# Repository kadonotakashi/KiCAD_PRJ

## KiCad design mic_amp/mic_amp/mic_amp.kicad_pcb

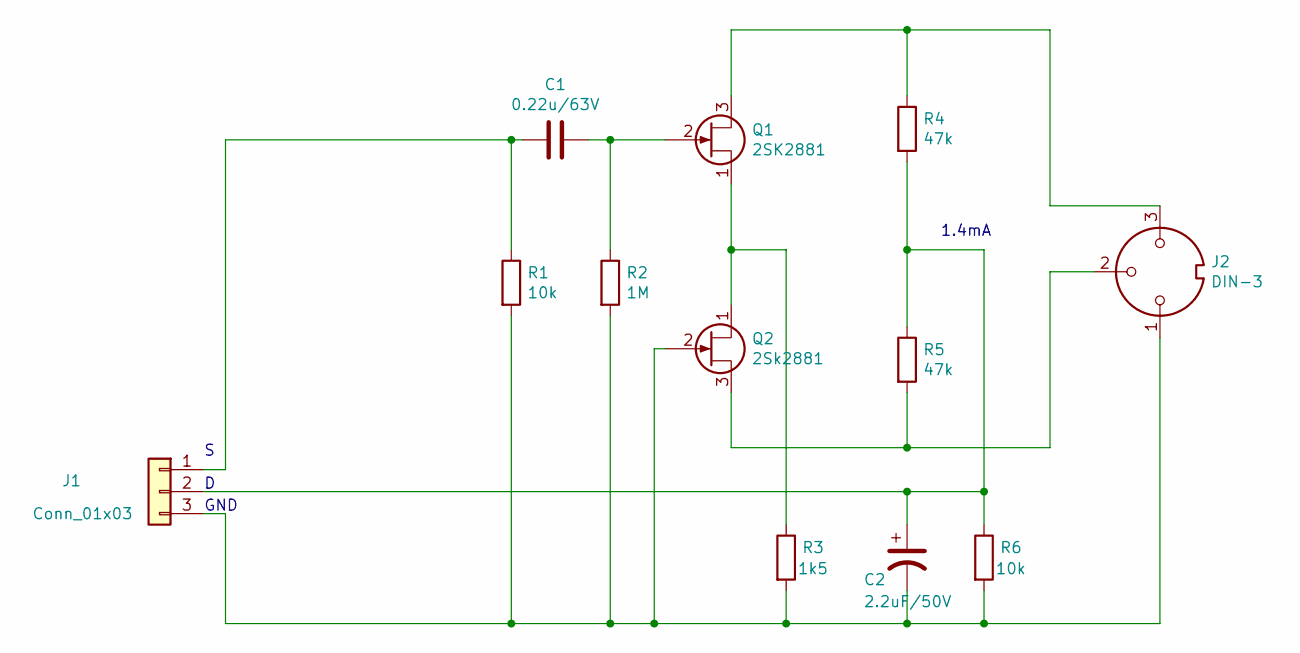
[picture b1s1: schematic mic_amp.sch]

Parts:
C1: 0.22u/63V; C_Disc_D7.5mm_W4.4mm_P5.00mm
C2: 2.2uF/50V; C_Radial_D5.0mm_H7.0mm_P2.00mm
J1: Conn_01x03; PinHeader_1x03_P2.54mm_Vertical
J2: DIN-3; PinHeader_1x03_P2.54mm_Vertical
Q1: 2SK2881; TO-92_Inline_Wide
Q2: 2Sk2881; TO-92_Inline_Wide
R1, R6: 10k; R_Axial_DIN0204_L3.6mm_D1.6mm_P7.62mm_Horizontal
R2: 1M; R_Axial_DIN0204_L3.6mm_D1.6mm_P7.62mm_Horizontal
R3: 1k5; R_Axial_DIN0204_L3.6mm_D1.6mm_P7.62mm_Horizontal
R4, R5: 47k; R_Axial_DIN0204_L3.6mm_D1.6mm_P7.62mm_Horizontal

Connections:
unnamed: C1.1, Q1.2 (G), R2.1
unnamed: C1.2, J1.1, R1.1
unnamed: C2.1, J1.2, R4.2, R5.1, R6.1
unnamed: C2.2, J1.3, J2.1, Q2.2 (G), R1.2, R2.2, R3.2, R6.2
unnamed: J2.2, Q2.3 (D), R5.2
unnamed: J2.3, Q1.3 (D), R4.1
unnamed: Q1.1 (S), Q2.1 (S), R3.1

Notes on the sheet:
1.4mA
GND

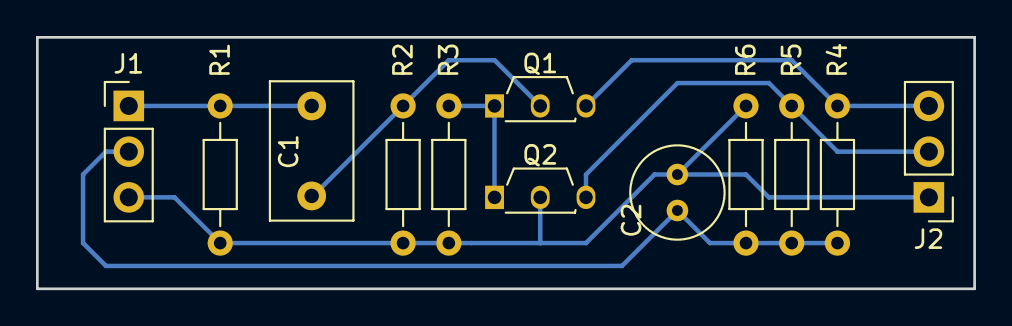
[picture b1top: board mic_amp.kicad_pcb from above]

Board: 2 copper layers, 52.1 x 14.0 mm, 12 parts (0 on the bottom side), 7 nets.

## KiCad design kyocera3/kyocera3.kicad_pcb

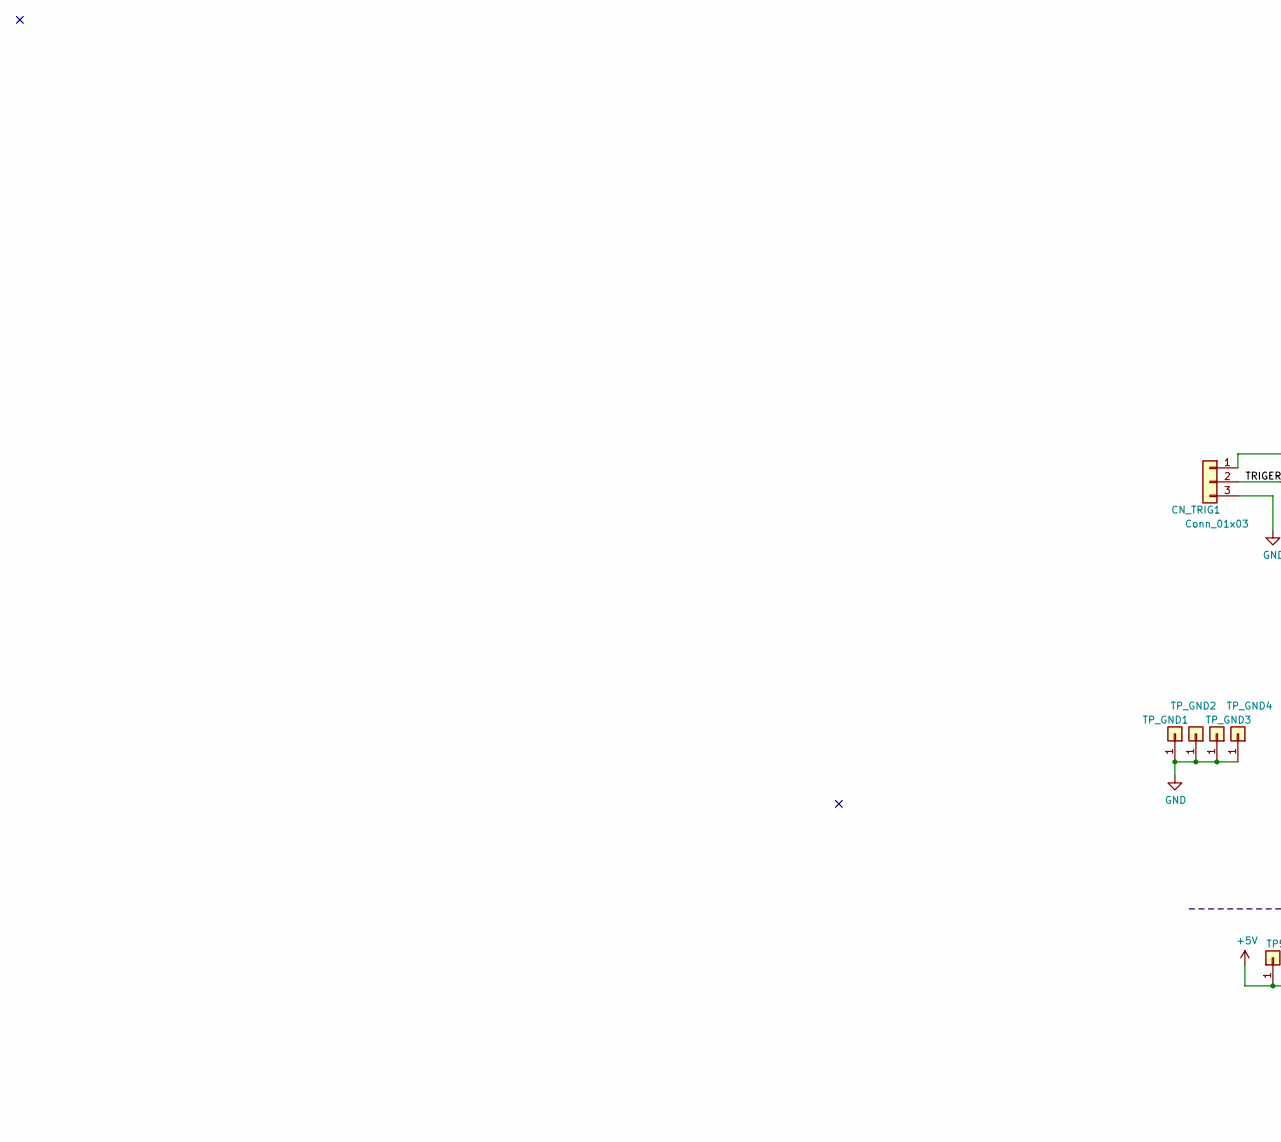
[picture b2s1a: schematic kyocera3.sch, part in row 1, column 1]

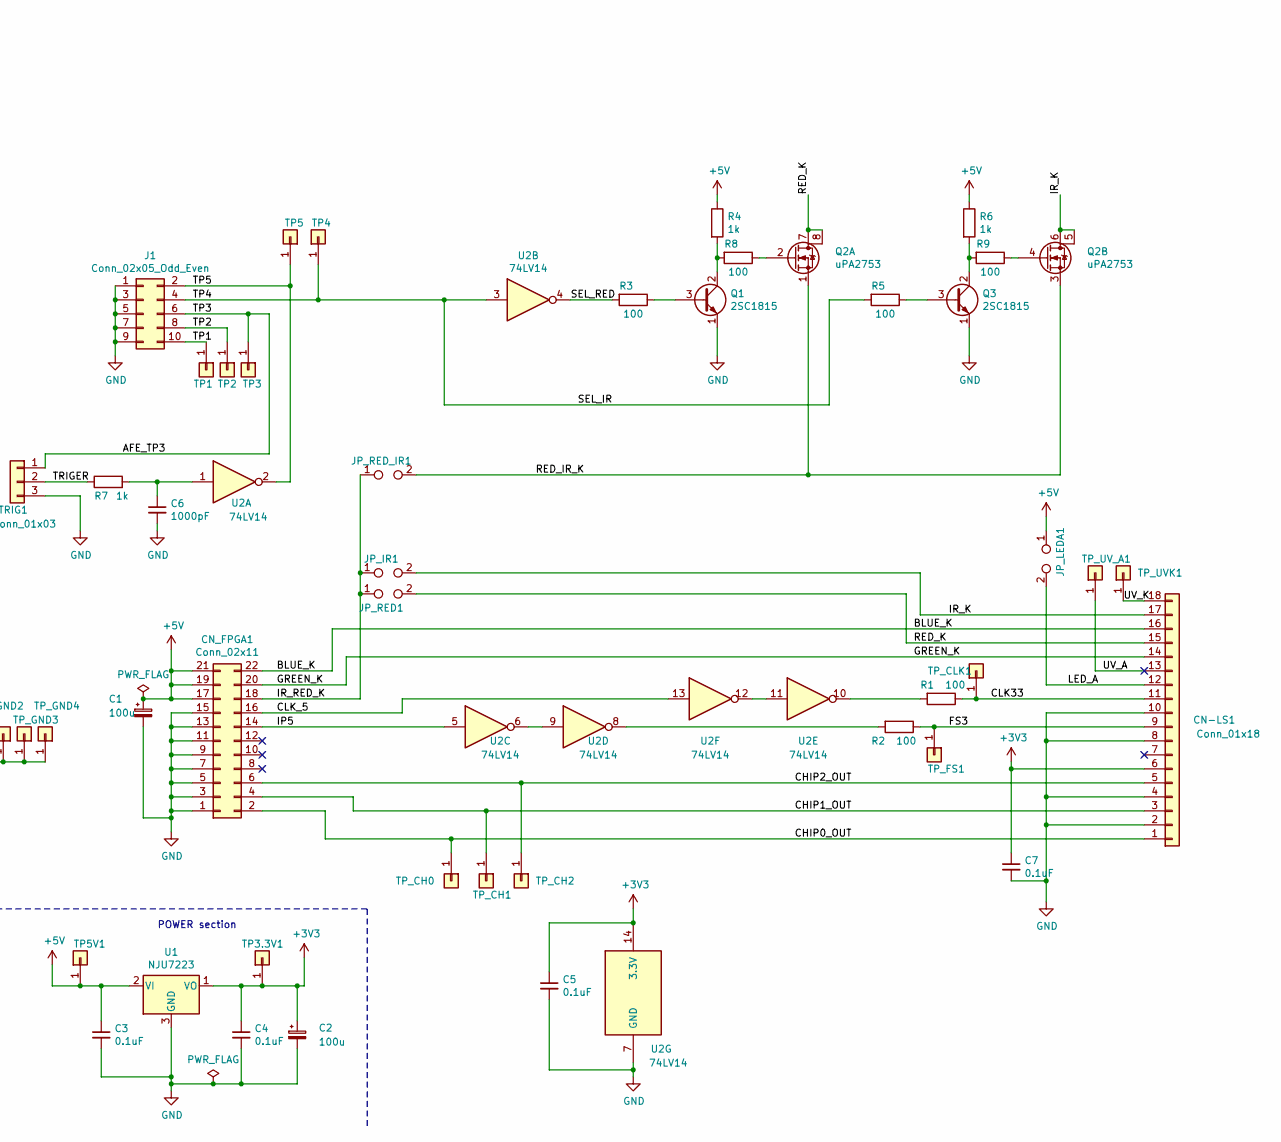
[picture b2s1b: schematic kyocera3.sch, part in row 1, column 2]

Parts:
C1, C2: 100u; CP_Radial_D6.3mm_P2.50mm
C3, C4, C5, C7: 0.1uF; C_0805_2012Metric_Pad1.15x1.40mm_HandSolder
C6: 1000pF; C_0805_2012Metric_Pad1.15x1.40mm_HandSolder
CN-LS1: Conn_01x18; TE_1-84953-8_1x18-1MP_P1.0mm_Horizontal
CN_FPGA1: Conn_02x11; PinHeader_2x11_P2.54mm_Vertical
CN_TRIG1: Conn_01x03; JST_EH_S03B-EH_1x03_P2.50mm_Horizontal
J1: Conn_02x05_Odd_Even; PinHeader_2x05_P2.54mm_Vertical
JP_IR1: IR; PinHeader_1x02_P2.54mm_Vertical
JP_LEDA1: IR; PinHeader_1x02_P2.54mm_Vertical
JP_RED1: RED; PinHeader_1x02_P2.54mm_Vertical
JP_RED_IR1: IR; PinHeader_1x02_P2.54mm_Vertical
Q1, Q3: 2SC1815; TO-92_Inline
Q2: uPA2753; SOIC-8_3.9x4.9mm_P1.27mm
R1, R2, R3, R5, R8, R9: 100; R_0805_2012Metric_Pad1.15x1.40mm_HandSolder
R4, R6, R7: 1k; R_0805_2012Metric_Pad1.15x1.40mm_HandSolder
TP1: _TP1; PinHeader_1x01_P2.54mm_Vertical
TP2: _TP2; PinHeader_1x01_P2.54mm_Vertical
TP3: _TP3; PinHeader_1x01_P2.54mm_Vertical
TP3.3V1: _TP33; PinHeader_1x01_P2.54mm_Vertical
TP4: _TP4; PinHeader_1x01_P2.54mm_Vertical
TP5: _TP5; PinHeader_1x01_P2.54mm_Vertical
TP5V1: _TP5V; PinHeader_1x01_P2.54mm_Vertical
TP_CH0: CH0; PinHeader_1x01_P2.54mm_Vertical
TP_CH1: CH1; PinHeader_1x01_P2.54mm_Vertical
TP_CH2: CH2; PinHeader_1x01_P2.54mm_Vertical
TP_CLK1: _CLK; PinHeader_1x01_P2.54mm_Vertical
TP_FS1: _FS; PinHeader_1x01_P2.54mm_Vertical
TP_GND1, TP_GND2, TP_GND3, TP_GND4: _GND; PinHeader_1x01_P2.54mm_Vertical
TP_UVK1: _CLK; PinHeader_1x01_P2.54mm_Vertical
TP_UV_A1: _CLK; PinHeader_1x01_P2.54mm_Vertical
U1: NJU7223; TO-252-3_TabPin2
U2: 74LV14; SOIC-14_3.9x8.7mm_P1.27mm

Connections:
+3V3: C2.1, C4.1, C5.1, C7.1, CN-LS1.6, TP3.3V1.1, U1.1 (VO), U2.14 (3.3V)
+5V: C1.1, C3.1, CN_FPGA1.17, CN_FPGA1.19, CN_FPGA1.21, JP_LEDA1.1, R4.1, R6.1, TP5V1.1, U1.2 (VI)
/AFE_TP3: CN_TRIG1.1, J1.6, TP3.1
/BLUE_K: CN-LS1.16, CN_FPGA1.22
/CHIP0_OUT: CN-LS1.1, CN_FPGA1.2, TP_CH0.1
/CHIP1_OUT: CN-LS1.3, CN_FPGA1.4, TP_CH1.1
/CHIP2_OUT: CN-LS1.5, CN_FPGA1.6, TP_CH2.1
/CLK33: CN-LS1.11, R1.1, TP_CLK1.1
/CLK_5: CN_FPGA1.16, U2.13
/FS3: CN-LS1.9, R2.1, TP_FS1.1
/GREEN_K: CN-LS1.14, CN_FPGA1.20
/IP5: CN_FPGA1.14, U2.5
/IR_K: CN-LS1.17, JP_IR1.2, Q2.5 (D), Q2.6 (D)
/IR_RED_K: CN_FPGA1.18, JP_IR1.1, JP_RED1.1, JP_RED_IR1.1
/LED_A: CN-LS1.12, JP_LEDA1.2
/RED_IR_K: JP_RED_IR1.2, Q2.1 (3S), Q2.3 (3S)
/RED_K: CN-LS1.15, JP_RED1.2, Q2.7 (D), Q2.8 (D)
/SEL_IR: J1.4, R5.2, TP4.1, U2.3
/SEL_RED: R3.2, U2.4
/TP1: J1.10, TP1.1
/TP2: J1.8, TP2.1
/TP5: J1.2, TP5.1, U2.2
/TRIGER: CN_TRIG1.2, R7.1
/UV_A: CN-LS1.13, TP_UV_A1.1
/UV_K: CN-LS1.18, TP_UVK1.1
GND: C1.2, C2.2, C3.2, C4.2, C5.2, C6.2, C7.2, CN-LS1.2, CN-LS1.4, CN-LS1.8, CN-LS1.10, CN_FPGA1.1, CN_FPGA1.3, CN_FPGA1.5, CN_FPGA1.7, CN_FPGA1.9, CN_FPGA1.11, CN_FPGA1.13, CN_FPGA1.15, CN_TRIG1.3, J1.1, J1.3, J1.5, J1.7, J1.9, Q1.1 (E), Q3.1 (E), TP_GND1.1, TP_GND2.1, TP_GND3.1, TP_GND4.1, U1.3 (GND), U2.7 (GND)
unnamed: C6.1, R7.2, U2.1
unnamed: Q1.2 (C), R4.2, R8.2
unnamed: Q1.3 (B), R3.1
unnamed: Q2.2 (G), R8.1
unnamed: Q2.4 (G), R9.1
unnamed: Q3.2 (C), R6.2, R9.2
unnamed: Q3.3 (B), R5.1
unnamed: R1.2, U2.10
unnamed: R2.2, U2.8
unnamed: U2.6, U2.9
unnamed: U2.11, U2.12

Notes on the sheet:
POWER section

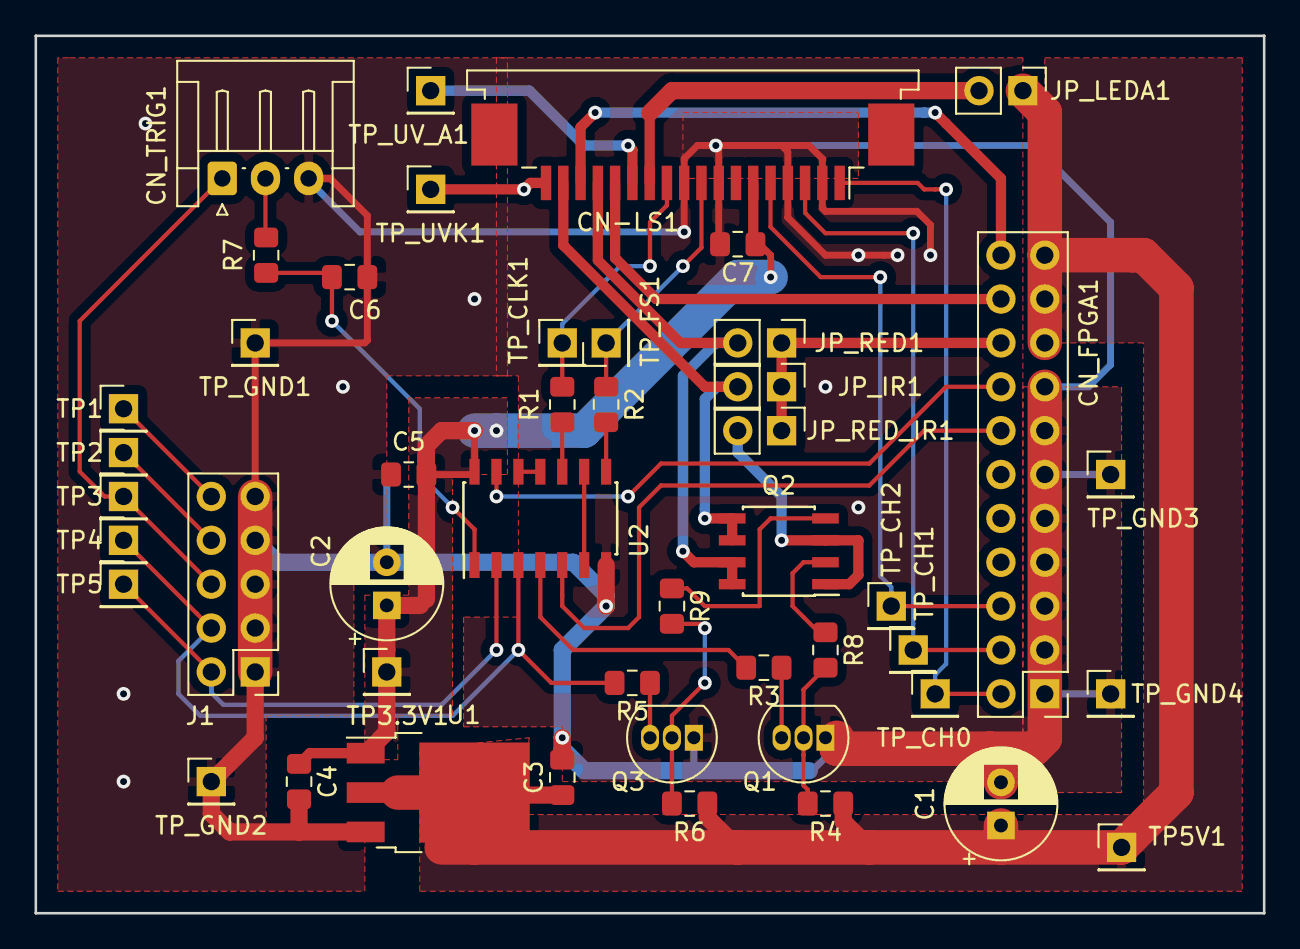
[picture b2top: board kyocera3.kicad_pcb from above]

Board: 2 copper layers, 71.1 x 50.8 mm, 47 parts (0 on the bottom side), 37 nets.

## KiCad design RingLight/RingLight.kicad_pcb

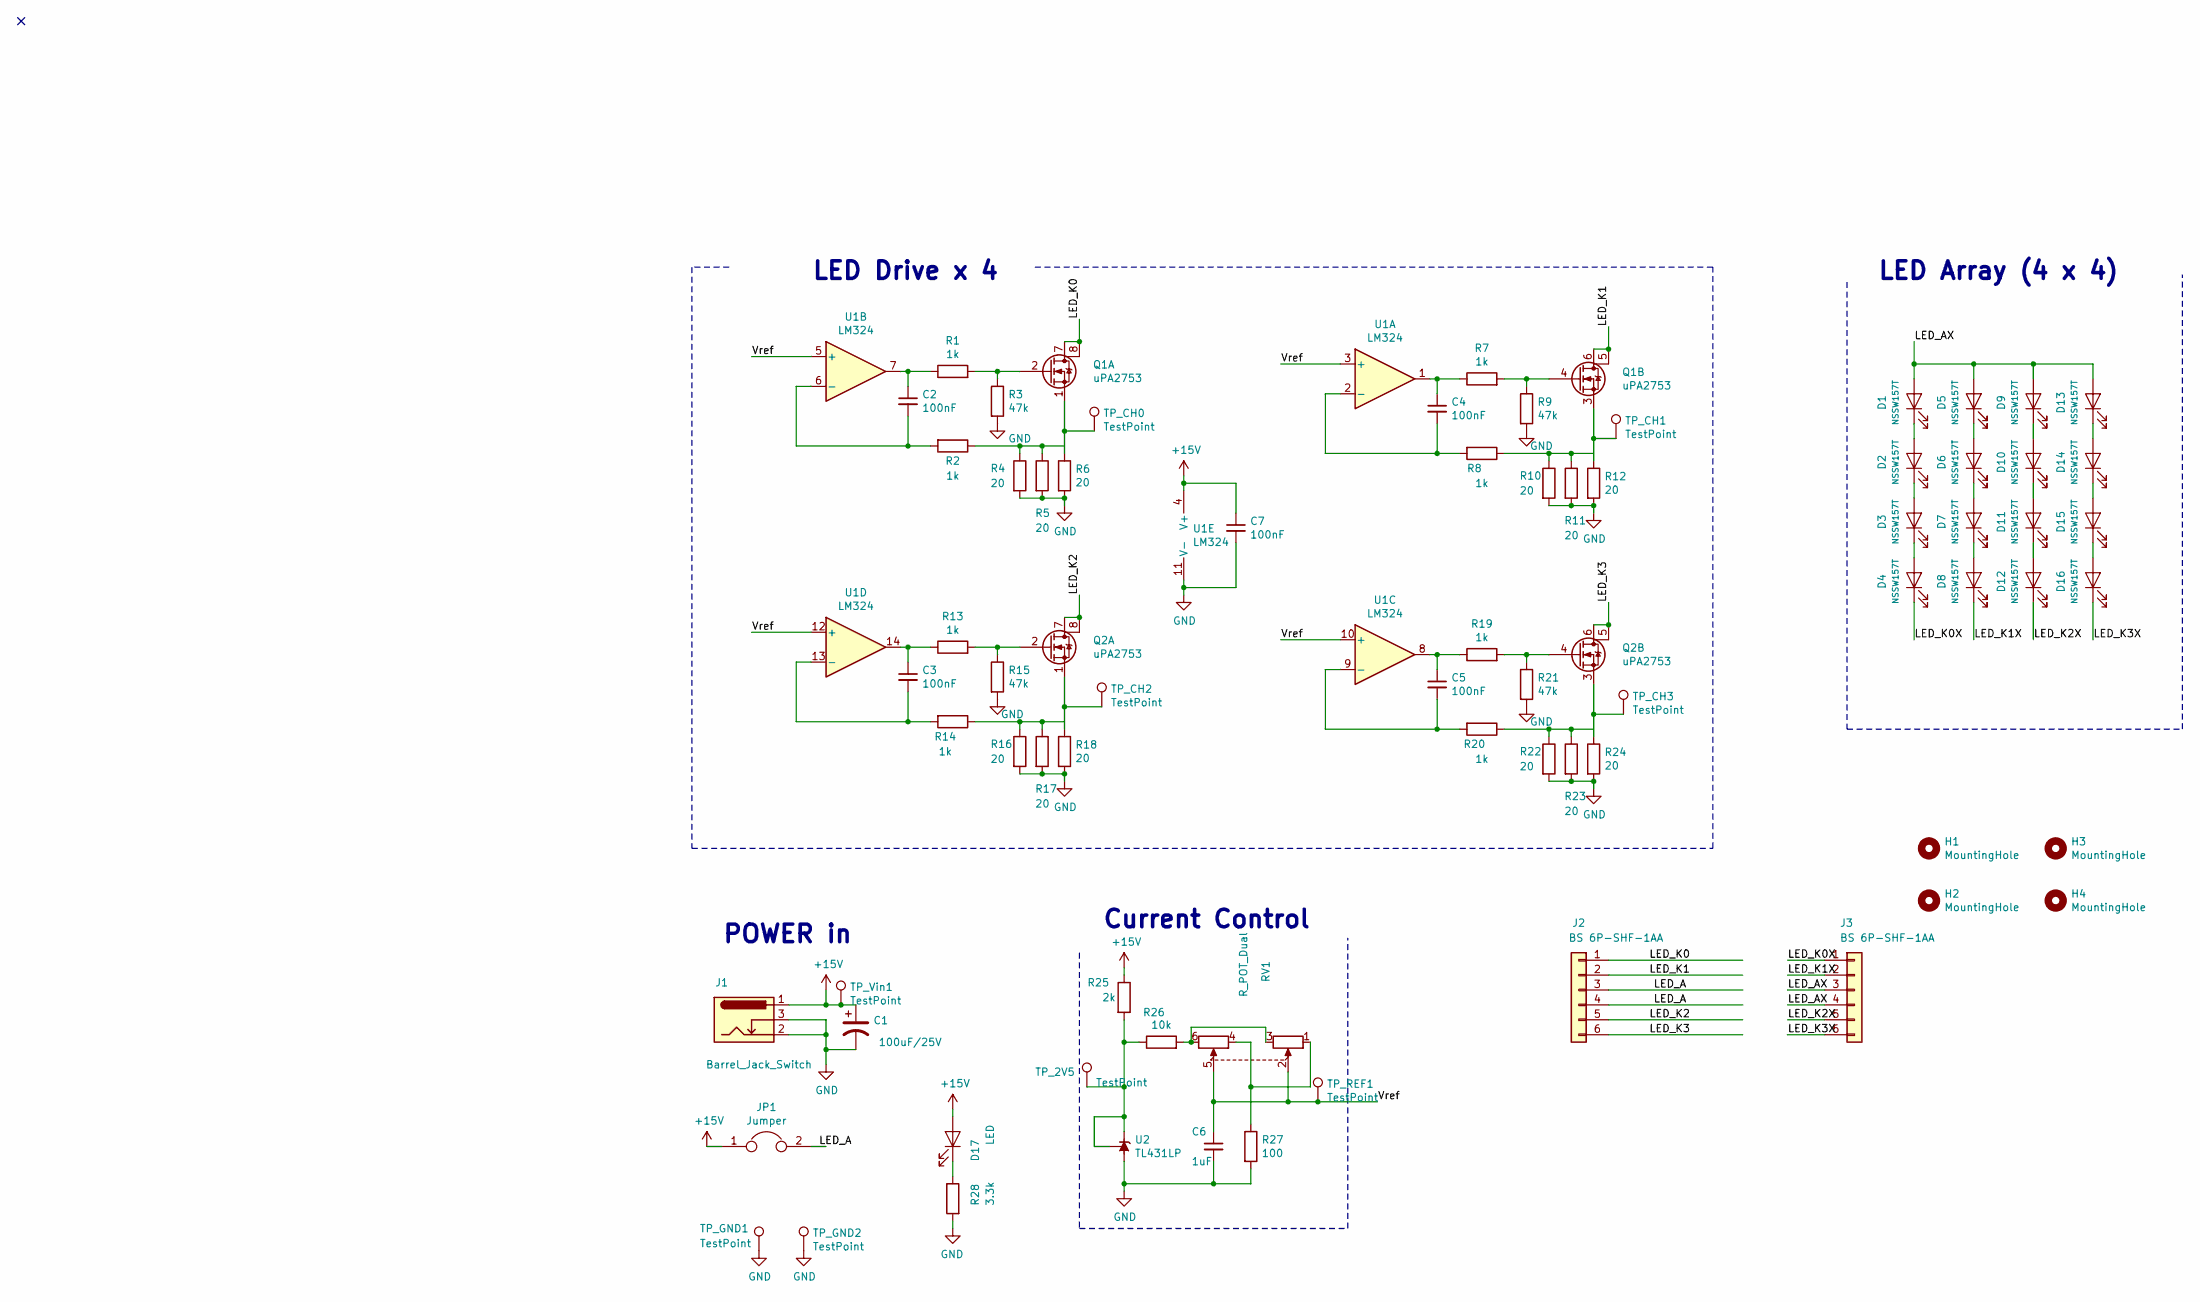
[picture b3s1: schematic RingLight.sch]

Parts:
C1: 100uF/25V; CP_Radial_D7.5mm_P2.50mm
C2, C3, C4, C5, C7: 100nF; C_0603_1608Metric_Pad1.05x0.95mm_HandSolder
C6: 1uF; C_0603_1608Metric_Pad1.05x0.95mm_HandSolder
D1, D2, D3, D4, D5, D6, D7, D8, D9, D10, D11, D12, D13, D14, D15, D16: NSSW157T; LED_1210_3225Metric_Pad1.42x2.65mm_HandSolder
D17: LED; LED_D3.0mm
H1, H2, H3, H4: MountingHole; MountingHole_3.2mm_M3
J1: Barrel_Jack_Switch; BarrelJack_Horizontal
J2, J3: BS 6P-SHF-1AA; JST_XH_B06B-XH-A_1x06_P2.50mm_Vertical
JP1: Jumper; PinHeader_1x02_P2.54mm_Vertical
Q1, Q2: uPA2753; SOIC-8_3.9x4.9mm_P1.27mm
R1, R2, R7, R8, R13, R14, R19, R20: 1k; R_0603_1608Metric_Pad1.05x0.95mm_HandSolder
R3, R9, R15, R21: 47k; R_0603_1608Metric_Pad1.05x0.95mm_HandSolder
R4, R5, R6, R10, R11, R12, R16, R17, R18, R22, R23, R24: 20; R_0603_1608Metric_Pad1.05x0.95mm_HandSolder
R25: 2k; R_0603_1608Metric_Pad1.05x0.95mm_HandSolder
R26: 10k; R_0603_1608Metric_Pad1.05x0.95mm_HandSolder
R27: 100; R_0603_1608Metric_Pad1.05x0.95mm_HandSolder
R28: 3.3k; R_0603_1608Metric_Pad1.05x0.95mm_HandSolder
RV1: R_POT_Dual; Potentiometer_Alps_RK097_Dual_Horizontal
TP_2V5: TestPoint; TestPoint_THTPad_1.5x1.5mm_Drill0.7mm
TP_CH0, TP_CH1, TP_CH2, TP_CH3: TestPoint; TestPoint_THTPad_1.5x1.5mm_Drill0.7mm
TP_GND1, TP_GND2: TestPoint; TestPoint_THTPad_1.5x1.5mm_Drill0.7mm
TP_REF1: TestPoint; TestPoint_THTPad_1.5x1.5mm_Drill0.7mm
TP_Vin1: TestPoint; TestPoint_THTPad_1.5x1.5mm_Drill0.7mm
U1: LM324; DIP-14_W7.62mm_LongPads
U2: TL431LP; TO-92_Inline_Wide

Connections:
+15V: C1.1, C7.1, D17.2 (A), J1.1, JP1.1, R25.1, TP_Vin1.1, U1.4 (V+)
/LED_A: J2.3, J2.4, JP1.2
/LED_AX: D1.2 (A), D5.2 (A), D9.2 (A), D13.2 (A), J3.3, J3.4
/LED_K0: J2.1, Q1.7 (D), Q1.8 (D)
/LED_K0X: D4.1 (K), J3.1
/LED_K1: J2.2, Q1.5 (D), Q1.6 (D)
/LED_K1X: D8.1 (K), J3.2
/LED_K2: J2.5, Q2.7 (D), Q2.8 (D)
/LED_K2X: D12.1 (K), J3.5
/LED_K3: J2.6, Q2.5 (D), Q2.6 (D)
/LED_K3X: D16.1 (K), J3.6
/Vref: C6.1, RV1.2, RV1.5, TP_REF1.1, U1.3 (+), U1.5 (+), U1.10 (+), U1.12 (+)
GND: C1.2, C6.2, C7.2, J1.2, J1.3, R3.2, R4.2, R5.2, R6.2, R9.2, R10.2, R11.2, R12.2, R15.2, R16.2, R17.2, R18.2, R21.2, R22.2, R23.2, R24.2, R27.2, R28.2, TP_GND1.1, TP_GND2.1, U1.11 (V-), U2.2 (A)
unnamed: C2.1, R1.1, U1.7
unnamed: C2.2, R2.2, U1.6 (-)
unnamed: C3.1, R13.1, U1.14
unnamed: C3.2, R14.2, U1.13 (-)
unnamed: C4.1, R7.1, U1.1
unnamed: C4.2, R8.2, U1.2 (-)
unnamed: C5.1, R19.1, U1.8
unnamed: C5.2, R20.2, U1.9 (-)
unnamed: D1.1 (K), D2.2 (A)
unnamed: D2.1 (K), D3.2 (A)
unnamed: D3.1 (K), D4.2 (A)
unnamed: D5.1 (K), D6.2 (A)
unnamed: D6.1 (K), D7.2 (A)
unnamed: D7.1 (K), D8.2 (A)
unnamed: D10.1 (K), D11.2 (A)
unnamed: D9.1 (K), D10.2 (A)
unnamed: D11.1 (K), D12.2 (A)
unnamed: D13.1 (K), D14.2 (A)
unnamed: D14.1 (K), D15.2 (A)
unnamed: D15.1 (K), D16.2 (A)
unnamed: D17.1 (K), R28.1
unnamed: Q1.1 (3S), R2.1, R4.1, R5.1, R6.1, TP_CH0.1
unnamed: Q1.2 (G), R1.2, R3.1
unnamed: Q1.3 (3S), R8.1, R10.1, R11.1, R12.1, TP_CH1.1
unnamed: Q1.4 (G), R7.2, R9.1
unnamed: Q2.1 (3S), R14.1, R16.1, R17.1, R18.1, TP_CH2.1
unnamed: Q2.2 (G), R13.2, R15.1
unnamed: Q2.3 (3S), R20.1, R22.1, R23.1, R24.1, TP_CH3.1
unnamed: Q2.4 (G), R19.2, R21.1
unnamed: R25.2, R26.1, TP_2V5.1, U2.1 (REF), U2.3 (K)
unnamed: R26.2, RV1.3, RV1.6
unnamed: R27.1, RV1.1, RV1.4

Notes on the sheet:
POWER in
Current Control
LED Drive x 4
LED Array (4 x 4)

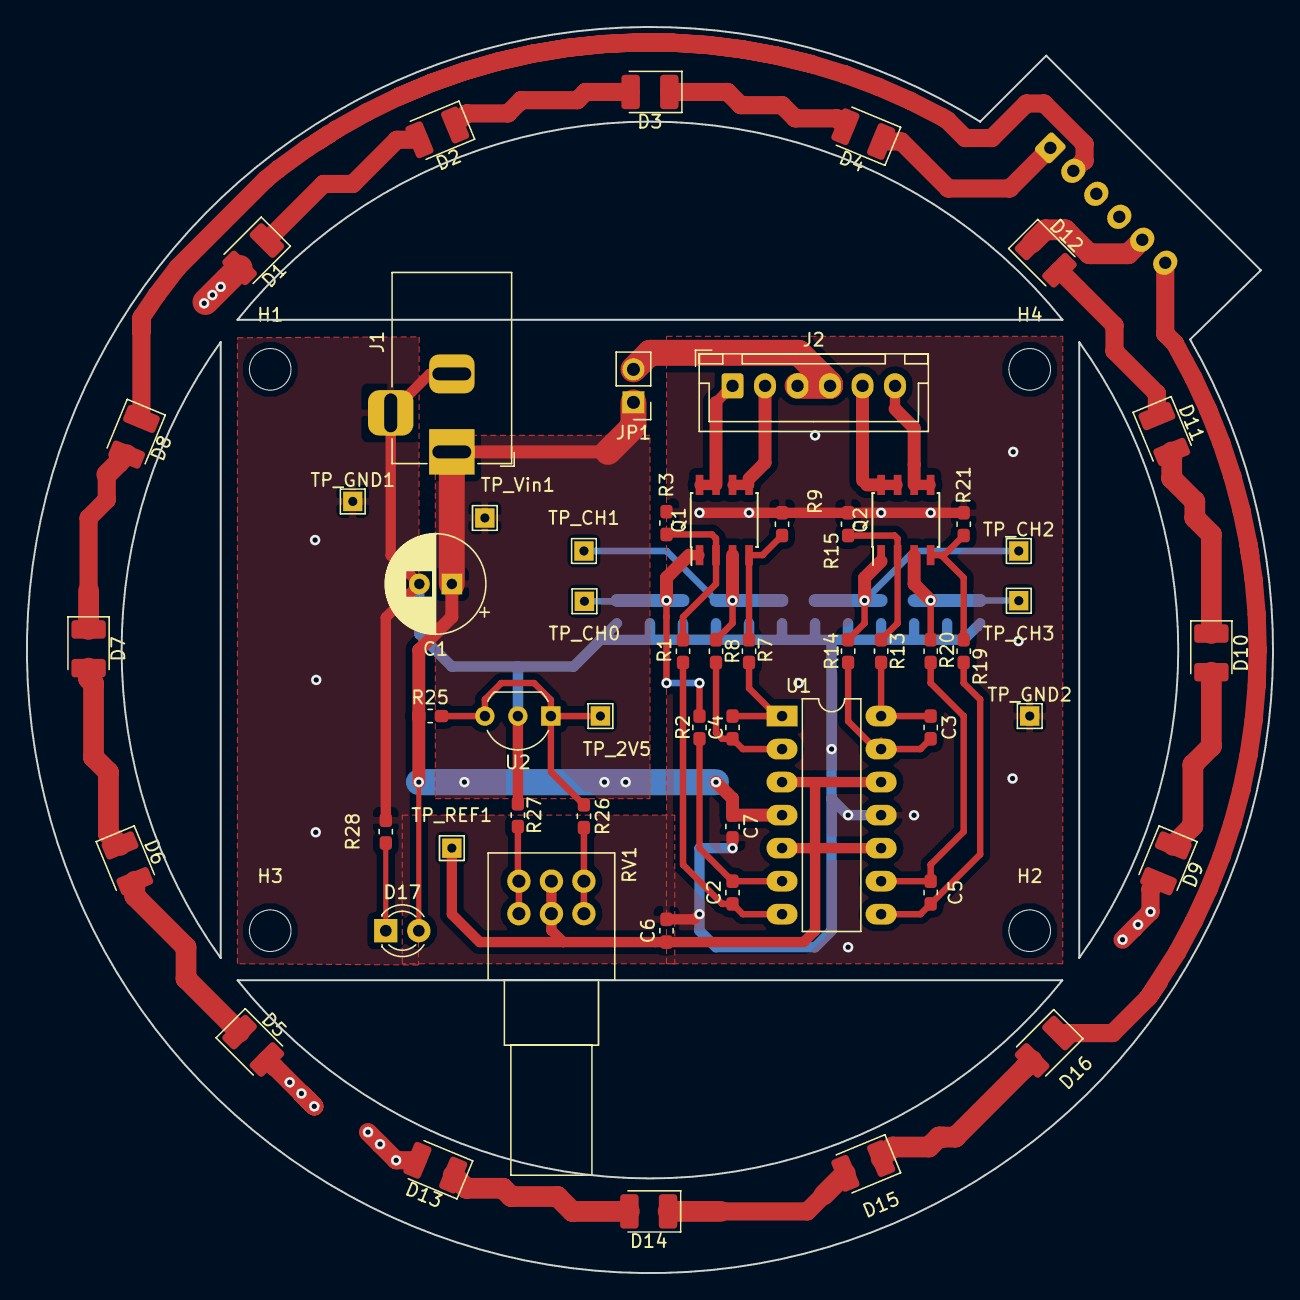
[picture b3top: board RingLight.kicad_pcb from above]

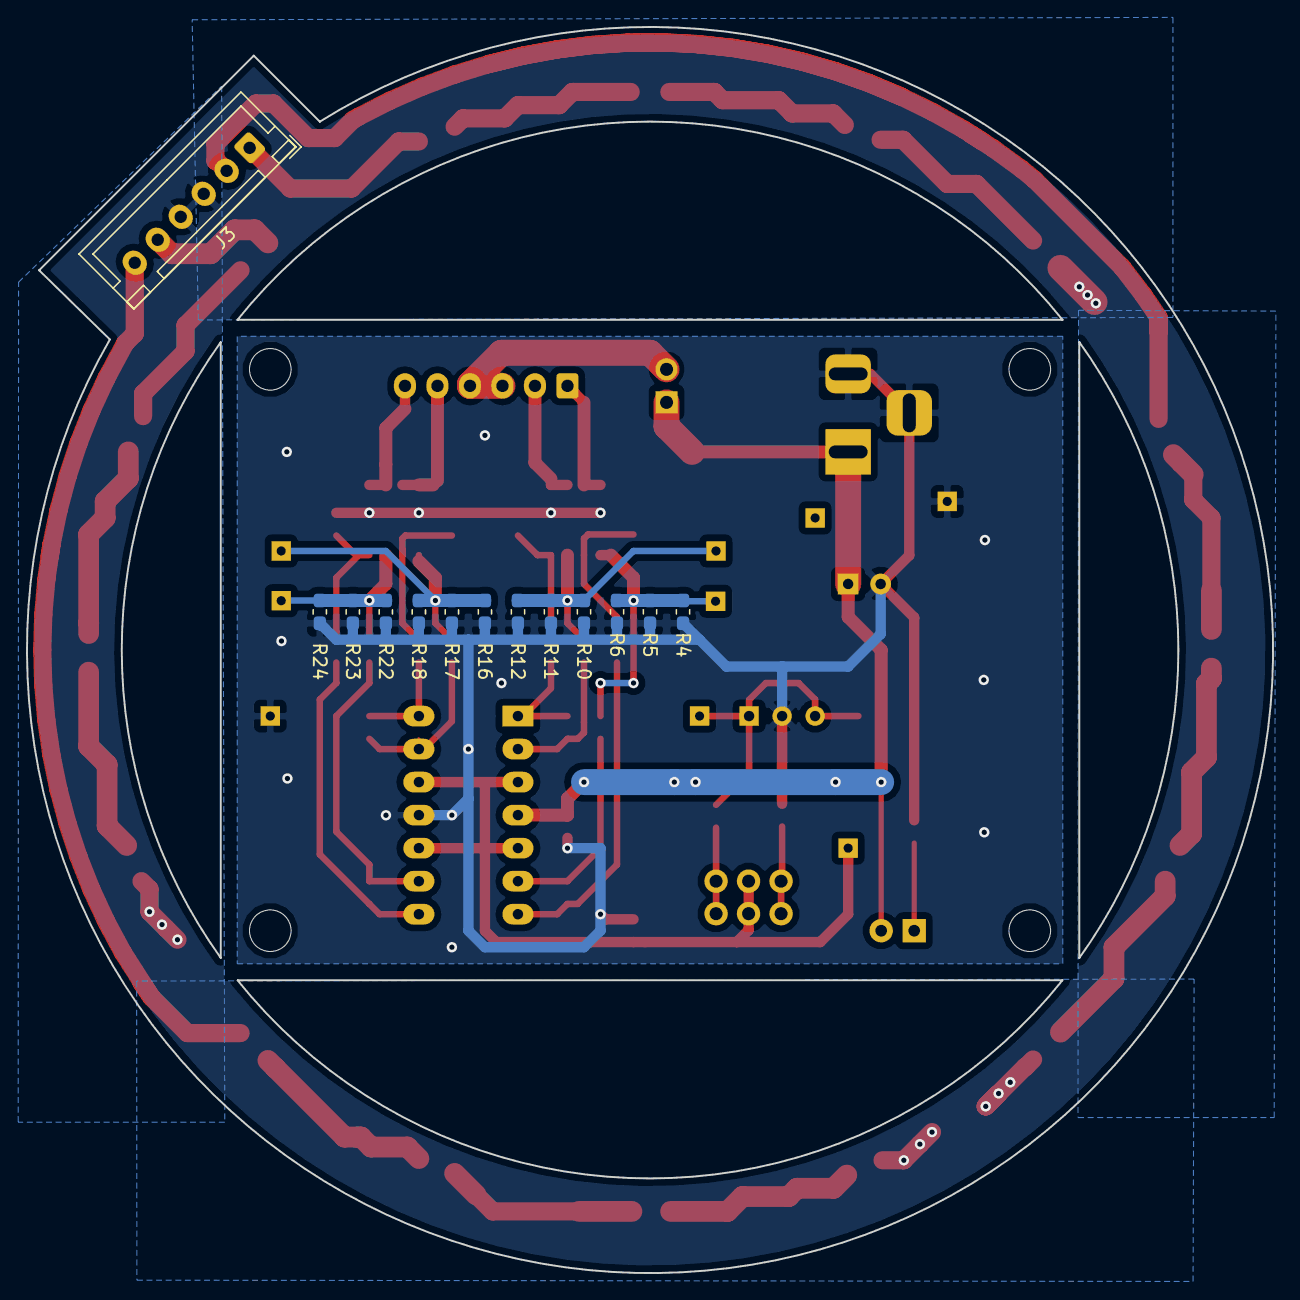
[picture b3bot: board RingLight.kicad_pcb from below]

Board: 2 copper layers, 95.8 x 95.8 mm, 74 parts (13 on the bottom side), 45 nets.

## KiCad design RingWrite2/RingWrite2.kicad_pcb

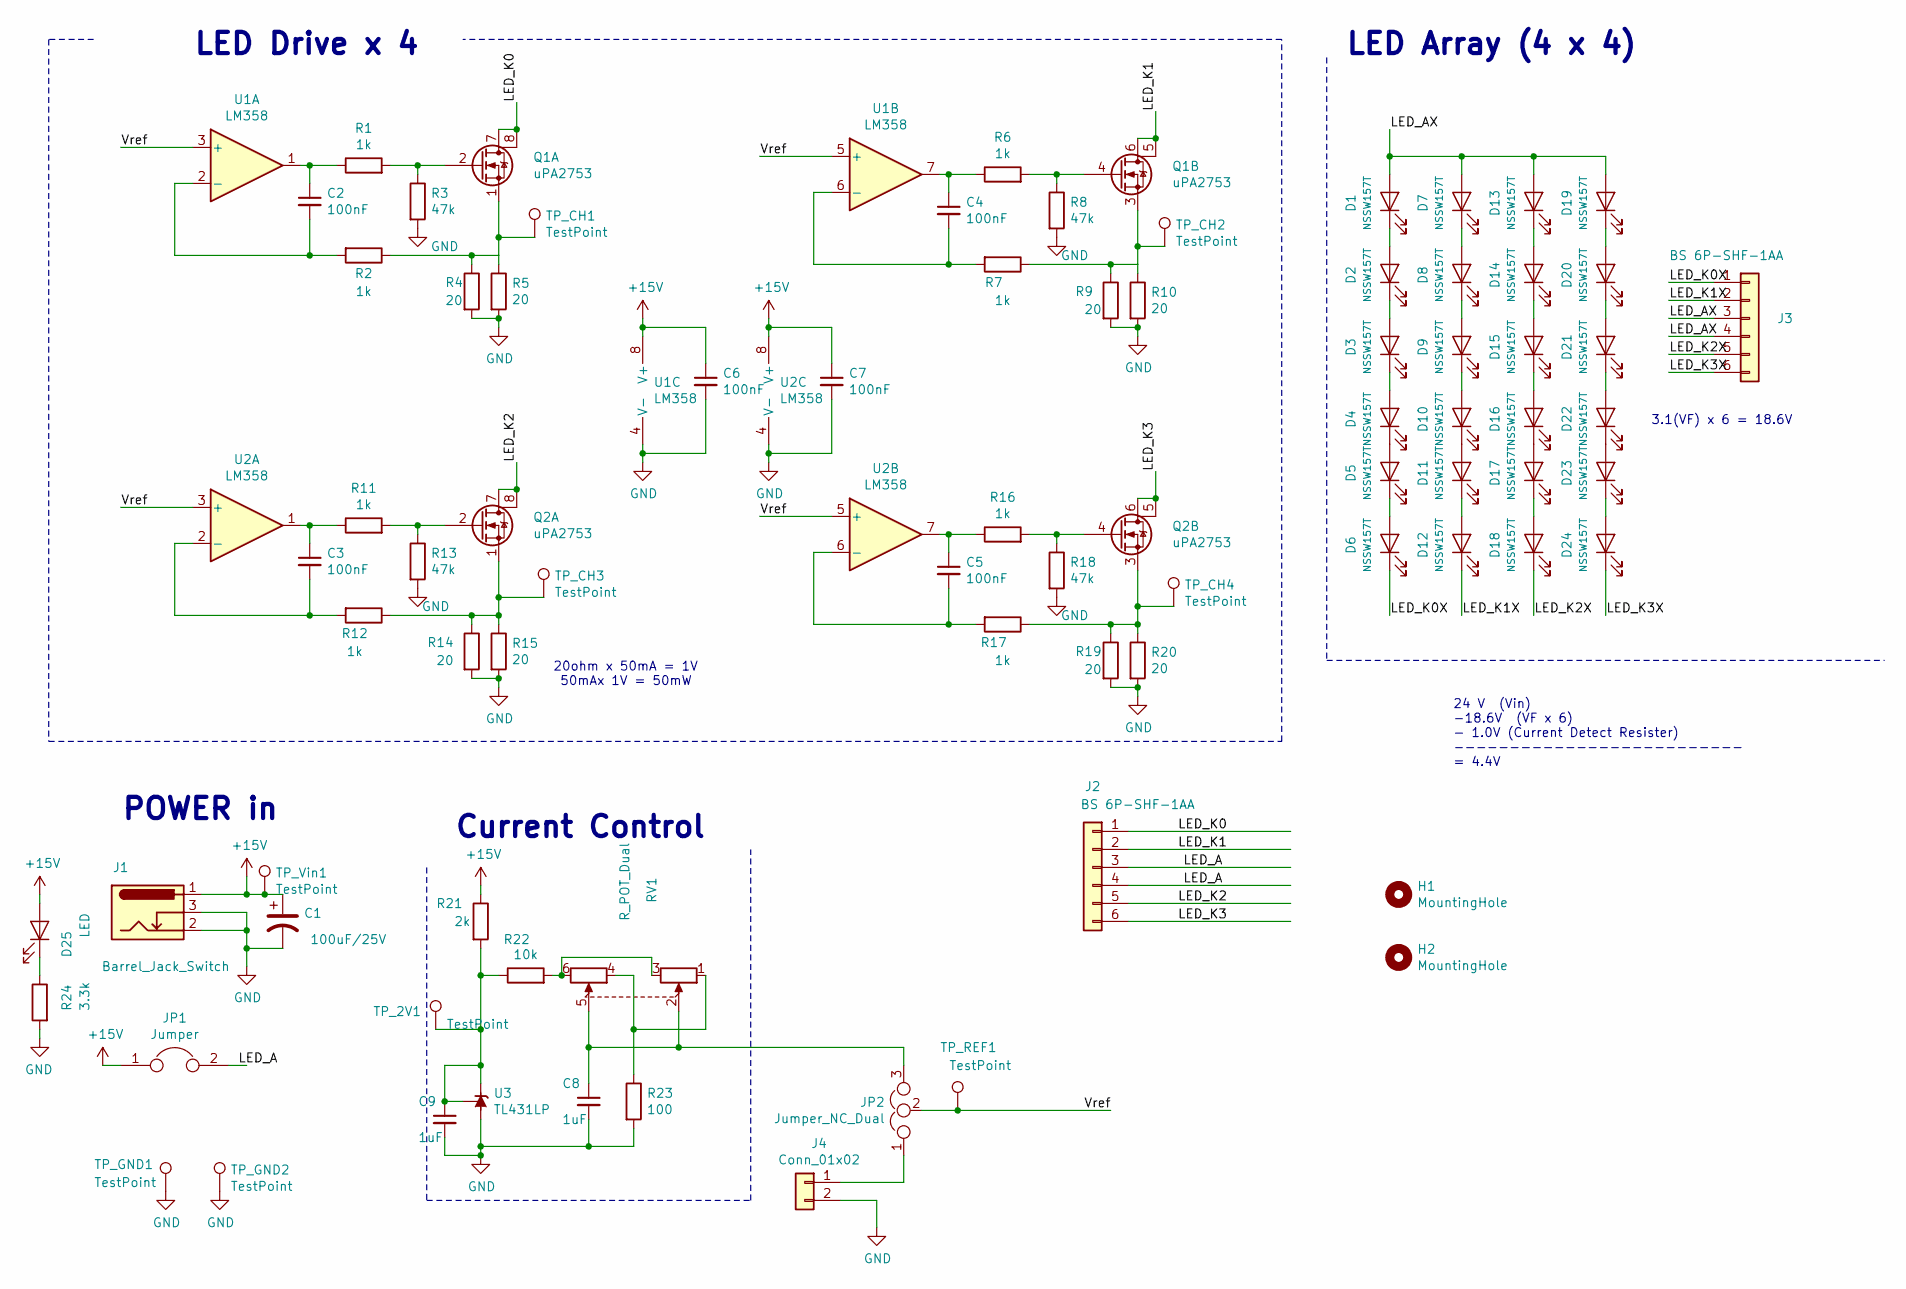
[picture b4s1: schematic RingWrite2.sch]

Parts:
C1: 100uF/25V; CP_Radial_D7.5mm_P2.50mm
C2, C3, C4, C5, C6, C7: 100nF; C_0603_1608Metric_Pad1.05x0.95mm_HandSolder
C8, C9: 1uF; C_0603_1608Metric_Pad1.05x0.95mm_HandSolder
D1, D2, D3, D4, D5, D6, D7, D8, D9, D10, D11, D12, D13, D14, D15, D16, D17, D18, D19, D20, D21, D22, D23, D24: NSSW157T; LED_1210_3225Metric_Pad1.42x2.65mm_HandSolder
D25: LED; LED_D3.0mm
H1, H2: MountingHole; MountingHole_3.2mm_M3
J1: Barrel_Jack_Switch; BarrelJack_Horizontal
J2, J3: BS 6P-SHF-1AA; JST_XH_B06B-XH-A_1x06_P2.50mm_Vertical
J4: Conn_01x02; JST_XH_B02B-XH-A_1x02_P2.50mm_Vertical
JP1: Jumper; PinHeader_1x02_P2.54mm_Vertical
JP2: Jumper_NC_Dual; PinHeader_1x03_P2.54mm_Vertical
Q1, Q2: uPA2753
R1, R2, R6, R7, R11, R12, R16, R17: 1k; R_0603_1608Metric_Pad1.05x0.95mm_HandSolder
R3, R8, R13, R18: 47k; R_0603_1608Metric_Pad1.05x0.95mm_HandSolder
R4, R5, R9, R10, R14, R15, R19, R20: 20; R_0603_1608Metric_Pad1.05x0.95mm_HandSolder
R21: 2k; R_0603_1608Metric_Pad1.05x0.95mm_HandSolder
R22: 10k; R_0603_1608Metric_Pad1.05x0.95mm_HandSolder
R23: 100; R_0603_1608Metric_Pad1.05x0.95mm_HandSolder
R24: 3.3k; R_0603_1608Metric_Pad1.05x0.95mm_HandSolder
RV1: R_POT_Dual; Potentiometer_Alps_RK097_Dual_Horizontal
TP_2V1: TestPoint; TestPoint_THTPad_1.5x1.5mm_Drill0.7mm
TP_CH1, TP_CH2, TP_CH3, TP_CH4: TestPoint; TestPoint_THTPad_1.5x1.5mm_Drill0.7mm
TP_GND1, TP_GND2: TestPoint; TestPoint_THTPad_1.5x1.5mm_Drill0.7mm
TP_REF1: TestPoint; TestPoint_THTPad_1.5x1.5mm_Drill0.7mm
TP_Vin1: TestPoint; TestPoint_THTPad_1.5x1.5mm_Drill0.7mm
U1, U2: LM358; SOIC-8_3.9x4.9mm_P1.27mm
U3: TL431LP; TO-92_Inline_Wide

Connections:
+15V: C1.1, C6.1, C7.1, D25.2 (A), J1.1, JP1.1, R21.1, TP_Vin1.1, U1.8 (V+), U2.8 (V+)
/LED_A: J2.3, J2.4, JP1.2
/LED_AX: D1.2 (A), D7.2 (A), D13.2 (A), D19.2 (A), J3.3, J3.4
/LED_K0: J2.1, Q1.7 (D), Q1.8 (D)
/LED_K0X: D6.1 (K), J3.1
/LED_K1: J2.2, Q1.5 (D), Q1.6 (D)
/LED_K1X: D12.1 (K), J3.2
/LED_K2: J2.5, Q2.7 (D), Q2.8 (D)
/LED_K2X: D18.1 (K), J3.5
/LED_K3: J2.6, Q2.5 (D), Q2.6 (D)
/LED_K3X: D24.1 (K), J3.6
/Vref: JP2.2, TP_REF1.1, U1.3 (+), U1.5 (+), U2.3 (+), U2.5 (+)
GND: C1.2, C6.2, C7.2, C8.2, C9.2, J1.2, J1.3, J4.2, R3.2, R4.2, R5.2, R8.2, R9.2, R10.2, R13.2, R14.2, R15.2, R18.2, R19.2, R20.2, R23.2, R24.2, TP_GND1.1, TP_GND2.1, U1.4 (V-), U2.4 (V-), U3.2 (A)
unnamed: C2.1, R1.1, U1.1
unnamed: C2.2, R2.2, U1.2 (-)
unnamed: C3.1, R11.1, U2.1
unnamed: C3.2, R12.2, U2.2 (-)
unnamed: C4.1, R6.1, U1.7
unnamed: C4.2, R7.2, U1.6 (-)
unnamed: C5.1, R16.1, U2.7
unnamed: C5.2, R17.2, U2.6 (-)
unnamed: C8.1, JP2.3, RV1.2, RV1.5
unnamed: C9.1, R21.2, R22.1, TP_2V1.1, U3.1 (REF), U3.3 (K)
unnamed: D1.1 (K), D2.2 (A)
unnamed: D2.1 (K), D3.2 (A)
unnamed: D3.1 (K), D4.2 (A)
unnamed: D4.1 (K), D5.2 (A)
unnamed: D5.1 (K), D6.2 (A)
unnamed: D7.1 (K), D8.2 (A)
unnamed: D8.1 (K), D9.2 (A)
unnamed: D10.1 (K), D11.2 (A)
unnamed: D9.1 (K), D10.2 (A)
unnamed: D11.1 (K), D12.2 (A)
unnamed: D13.1 (K), D14.2 (A)
unnamed: D14.1 (K), D15.2 (A)
unnamed: D15.1 (K), D16.2 (A)
unnamed: D16.1 (K), D17.2 (A)
unnamed: D17.1 (K), D18.2 (A)
unnamed: D19.1 (K), D20.2 (A)
unnamed: D20.1 (K), D21.2 (A)
unnamed: D21.1 (K), D22.2 (A)
unnamed: D22.1 (K), D23.2 (A)
unnamed: D23.1 (K), D24.2 (A)
unnamed: D25.1 (K), R24.1
unnamed: J4.1, JP2.1
unnamed: Q1.1 (3S), R2.1, R4.1, R5.1, TP_CH1.1
unnamed: Q1.2 (G), R1.2, R3.1
unnamed: Q1.3 (3S), R7.1, R9.1, R10.1, TP_CH2.1
unnamed: Q1.4 (G), R6.2, R8.1
unnamed: Q2.1 (3S), R12.1, R14.1, R15.1, TP_CH3.1
unnamed: Q2.2 (G), R11.2, R13.1
unnamed: Q2.3 (3S), R17.1, R19.1, R20.1, TP_CH4.1
unnamed: Q2.4 (G), R16.2, R18.1
unnamed: R22.2, RV1.3, RV1.6
unnamed: R23.1, RV1.1, RV1.4

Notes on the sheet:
POWER in
Current Control
LED Drive x 4
LED Array (4 x 4)
3.1(VF) x 6 = 18.6V
20ohm x 50mA = 1V 50mAx 1V = 50mW
24 V (Vin) -18.6V (VF x 6) - 1.0V (Current Detect Resister) -------------------------- = 4.4V
